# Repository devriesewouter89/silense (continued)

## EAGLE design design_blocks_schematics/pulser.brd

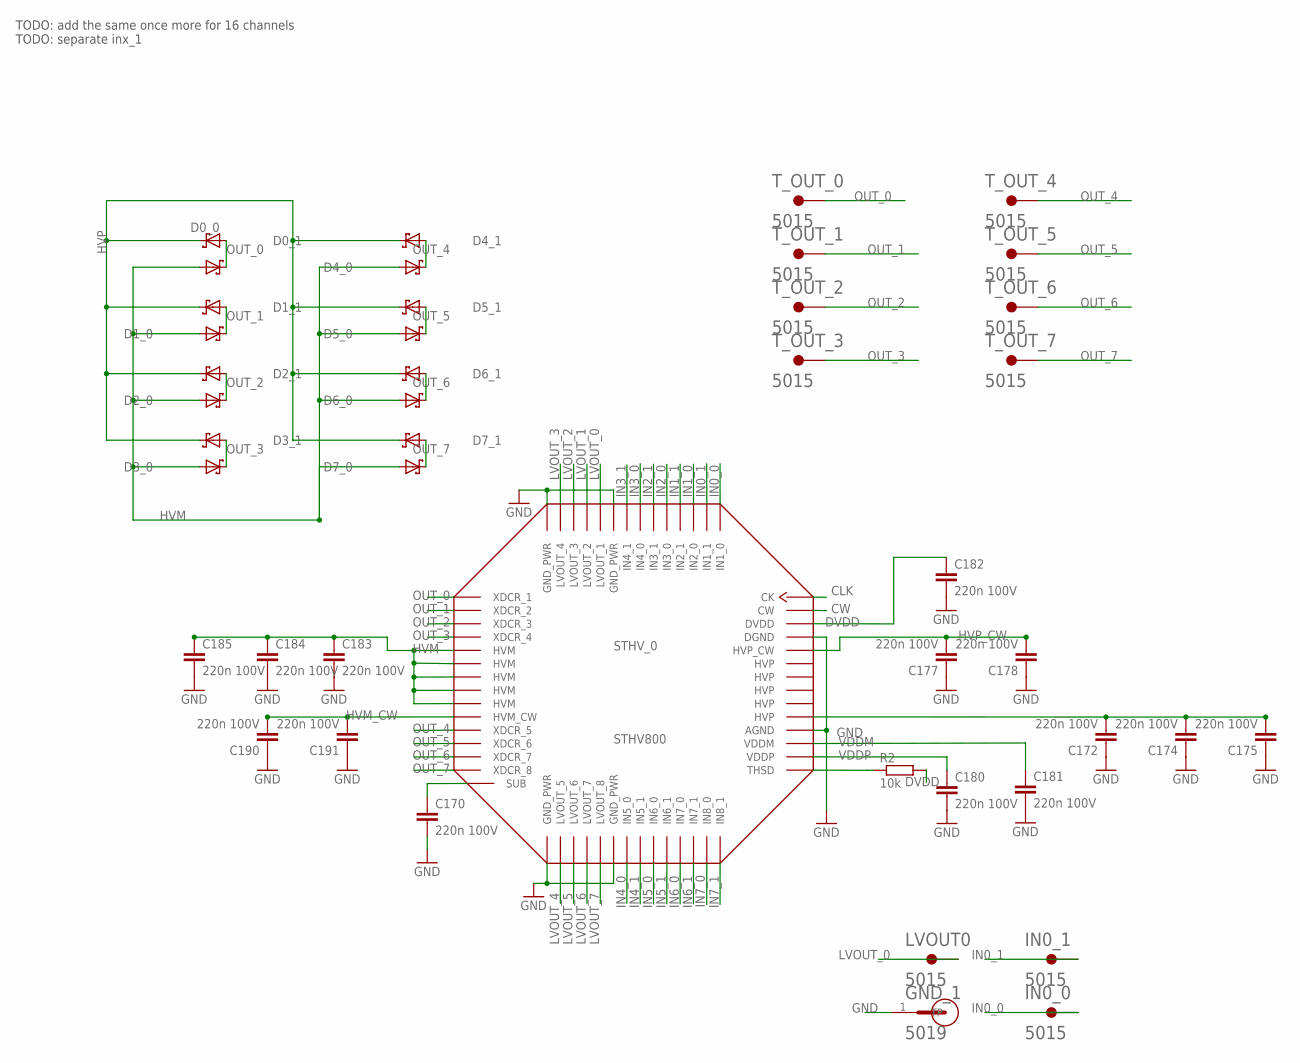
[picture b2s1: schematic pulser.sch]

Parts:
C170, C172, C174, C175, C177, C178, C180, C181, C182, C183, C184, C185, C190, C191: 220n 100V; C0805
D0_0, D0_1, D1_0, D1_1, D2_0, D2_1, D3_0, D3_1, D4_0, D4_1, D5_0, D5_1, D6_0, D6_1, D7_0, D7_1: SBR1U200P1SBR1U200P1; POWERDI-123
GND_1: 5019; TP380X203
IN0_0, IN0_1: 5015; KEYSTONE_5015
LVOUT0: 5015; KEYSTONE_5015
R2: 10k; R0805
STHV_0: STHV800; TFLGA-56LD
T_OUT_0, T_OUT_1, T_OUT_2, T_OUT_3, T_OUT_4, T_OUT_5, T_OUT_6, T_OUT_7: 5015; KEYSTONE_5015

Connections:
CLK: STHV_0.CK
CW: STHV_0.CW
GND: C170.2, C172.1, C174.1, C175.1, C177.1, C178.1, C180.2, C181.2, C182.2, C183.2, C184.2, C185.2, C190.1, C191.1, GND_1.1, STHV_0.AGND, STHV_0.DGND, STHV_0.GND_PWR@1 (GND_PWR), STHV_0.GND_PWR@2 (GND_PWR), STHV_0.GND_PWR@3 (GND_PWR), STHV_0.GND_PWR@4 (GND_PWR)
HVM: C183.1, C184.1, C185.1, D0_1.A, D1_1.A, D2_1.A, D3_1.A, D4_1.A, D5_1.A, D6_1.A, D7_1.A, STHV_0.HVM@1 (HVM), STHV_0.HVM@2 (HVM), STHV_0.HVM@3 (HVM), STHV_0.HVM@4 (HVM), STHV_0.HVM@5 (HVM)
HVM_CW: C190.2, C191.2, STHV_0.HVM_CW
HVP: C172.2, C174.2, C175.2, D0_0.C, D1_0.C, D2_0.C, D3_0.C, D4_0.C, D5_0.C, D6_0.C, D7_0.C, STHV_0.HVP@1 (HVP), STHV_0.HVP@2 (HVP), STHV_0.HVP@3 (HVP), STHV_0.HVP@4 (HVP), STHV_0.HVP@5 (HVP)
HVP_CW: C177.2, C178.2, STHV_0.HVP_CW
IN0_0: IN0_0.1, STHV_0.IN1_0
IN0_1: IN0_1.1, STHV_0.IN1_1
IN1_0: STHV_0.IN2_0
IN1_1: STHV_0.IN2_1
IN2_0: STHV_0.IN3_0
IN2_1: STHV_0.IN3_1
IN3_0: STHV_0.IN4_0
IN3_1: STHV_0.IN4_1
IN4_0: STHV_0.IN5_0
IN4_1: STHV_0.IN5_1
IN5_0: STHV_0.IN6_0
IN5_1: STHV_0.IN6_1
IN6_0: STHV_0.IN7_0
IN6_1: STHV_0.IN7_1
IN7_0: STHV_0.IN8_0
IN7_1: STHV_0.IN8_1
LVOUT_0: LVOUT0.1, STHV_0.LVOUT_1
LVOUT_1: STHV_0.LVOUT_2
LVOUT_2: STHV_0.LVOUT_3
LVOUT_3: STHV_0.LVOUT_4
LVOUT_4: STHV_0.LVOUT_5
LVOUT_5: STHV_0.LVOUT_6
LVOUT_6: STHV_0.LVOUT_7
LVOUT_7: STHV_0.LVOUT_8
unnamed: R2.1, STHV_0.THSD
unnamed: C170.1, STHV_0.SUB
OUT_0: D0_0.A, D0_1.C, STHV_0.XDCR_1, T_OUT_0.1
OUT_1: D1_0.A, D1_1.C, STHV_0.XDCR_2, T_OUT_1.1
OUT_2: D2_0.A, D2_1.C, STHV_0.XDCR_3, T_OUT_2.1
OUT_3: D3_0.A, D3_1.C, STHV_0.XDCR_4, T_OUT_3.1
OUT_4: D4_0.A, D4_1.C, STHV_0.XDCR_5, T_OUT_4.1
OUT_5: D5_0.A, D5_1.C, STHV_0.XDCR_6, T_OUT_5.1
OUT_6: D6_0.A, D6_1.C, STHV_0.XDCR_7, T_OUT_6.1
OUT_7: D7_0.A, D7_1.C, STHV_0.XDCR_8, T_OUT_7.1
VDDM: C181.1, STHV_0.VDDM
VDDP: C180.1, STHV_0.VDDP

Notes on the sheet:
TODO: add the same once more for 16 channels TODO: separate inx_1

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
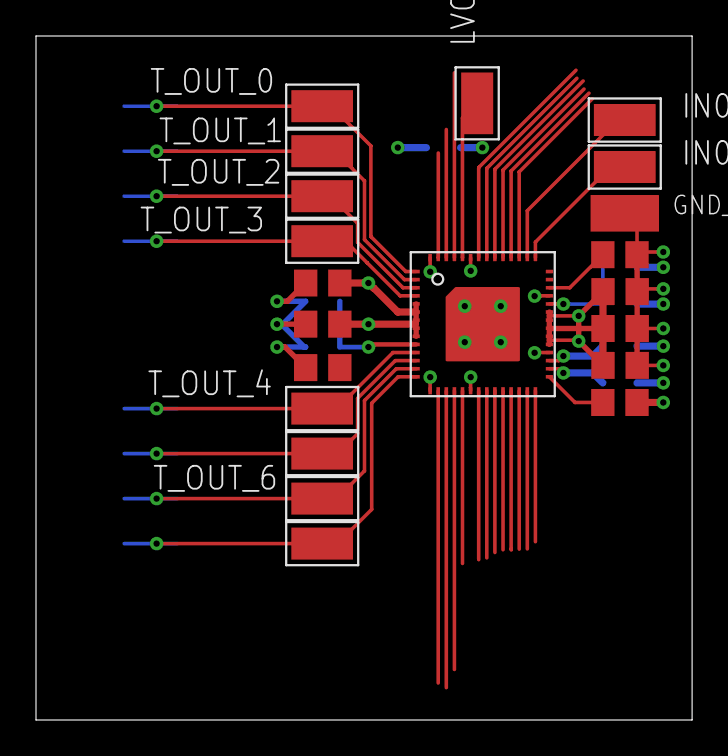
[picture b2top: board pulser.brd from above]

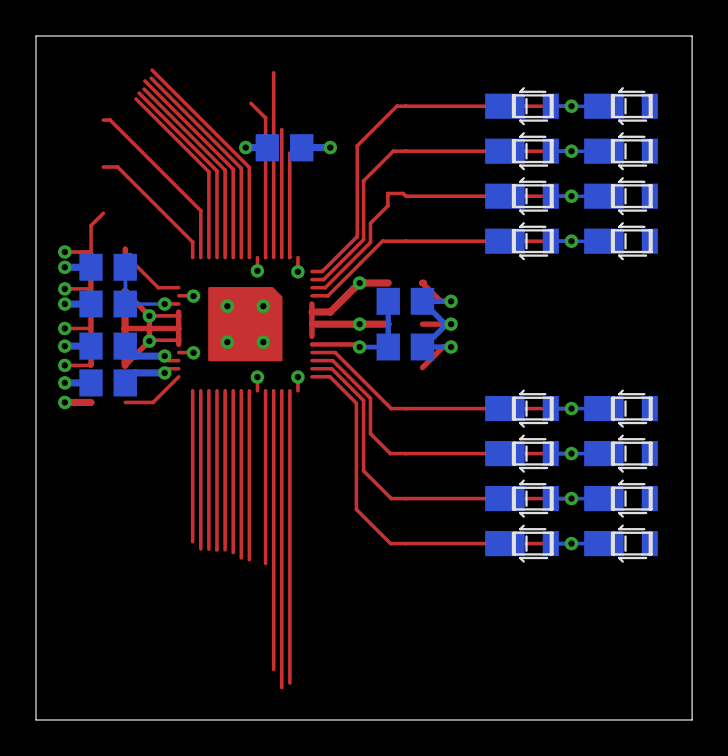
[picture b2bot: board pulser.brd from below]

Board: 2 copper layers, 36.5 x 38.0 mm, 44 parts (23 on the bottom side), 21 nets.

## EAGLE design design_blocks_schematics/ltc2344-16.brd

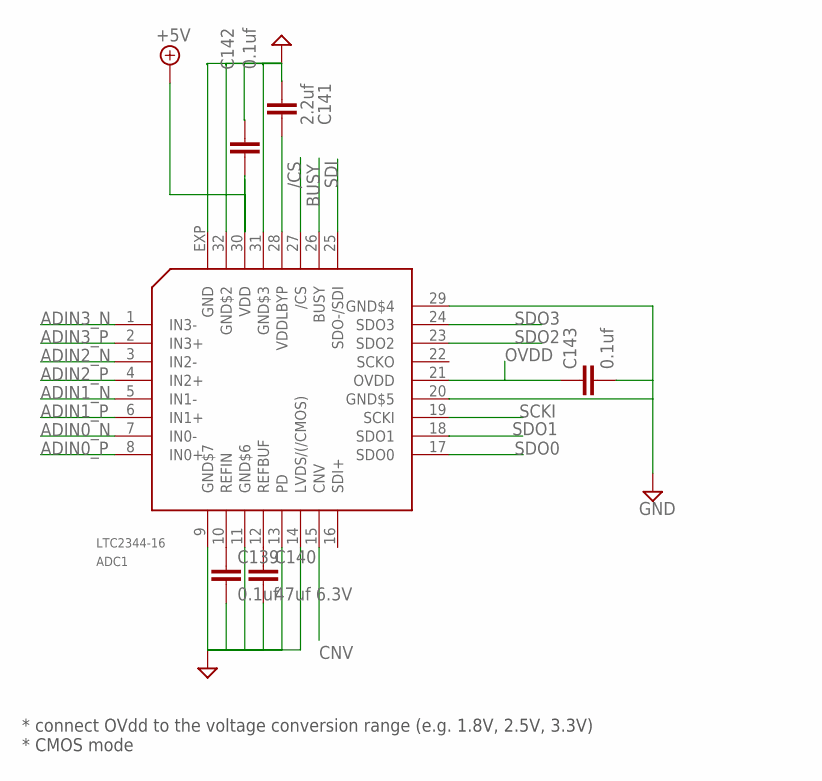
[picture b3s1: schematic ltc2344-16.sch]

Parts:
ADC1: LTC2344-16; QFN32
C139, C142, C143: 0.1uf; C0402
C140: 47uf 6.3V; C0603
C141: 2.2uf; C0402

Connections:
+5V: ADC1.30 (VDD), C142.1
/CS: ADC1.27 (/CS)
ADIN0_N: ADC1.7 (IN0-)
ADIN0_P: ADC1.8 (IN0+)
ADIN1_N: ADC1.5 (IN1-)
ADIN1_P: ADC1.6 (IN1+)
ADIN2_N: ADC1.3 (IN2-)
ADIN2_P: ADC1.4 (IN2+)
ADIN3_N: ADC1.1 (IN3-)
ADIN3_P: ADC1.2 (IN3+)
BUSY: ADC1.26 (BUSY)
CNV: ADC1.15 (CNV)
GND: ADC1.9 (GND$7), ADC1.11 (GND$6), ADC1.13 (PD), ADC1.14 (LVDS/(/CMOS)), ADC1.20 (GND$5), ADC1.29 (GND$4), ADC1.31 (GND$3), ADC1.32 (GND$2), ADC1.EXP (GND), C139.2, C140.2, C141.2, C142.2, C143.2
unnamed: ADC1.10 (REFIN), C139.1
unnamed: ADC1.12 (REFBUF), C140.1
unnamed: ADC1.28 (VDDLBYP), C141.1
OVDD: ADC1.21 (OVDD), C143.1
SCKI: ADC1.19 (SCKI)
SDI: ADC1.25 (SDO-/SDI)
SDO0: ADC1.17 (SDO0)
SDO1: ADC1.18 (SDO1)
SDO2: ADC1.23 (SDO2)
SDO3: ADC1.24 (SDO3)

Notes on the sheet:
* connect OVdd to the voltage conversion range (e.g. 1.8V, 2.5V, 3.3V) * CMOS mode

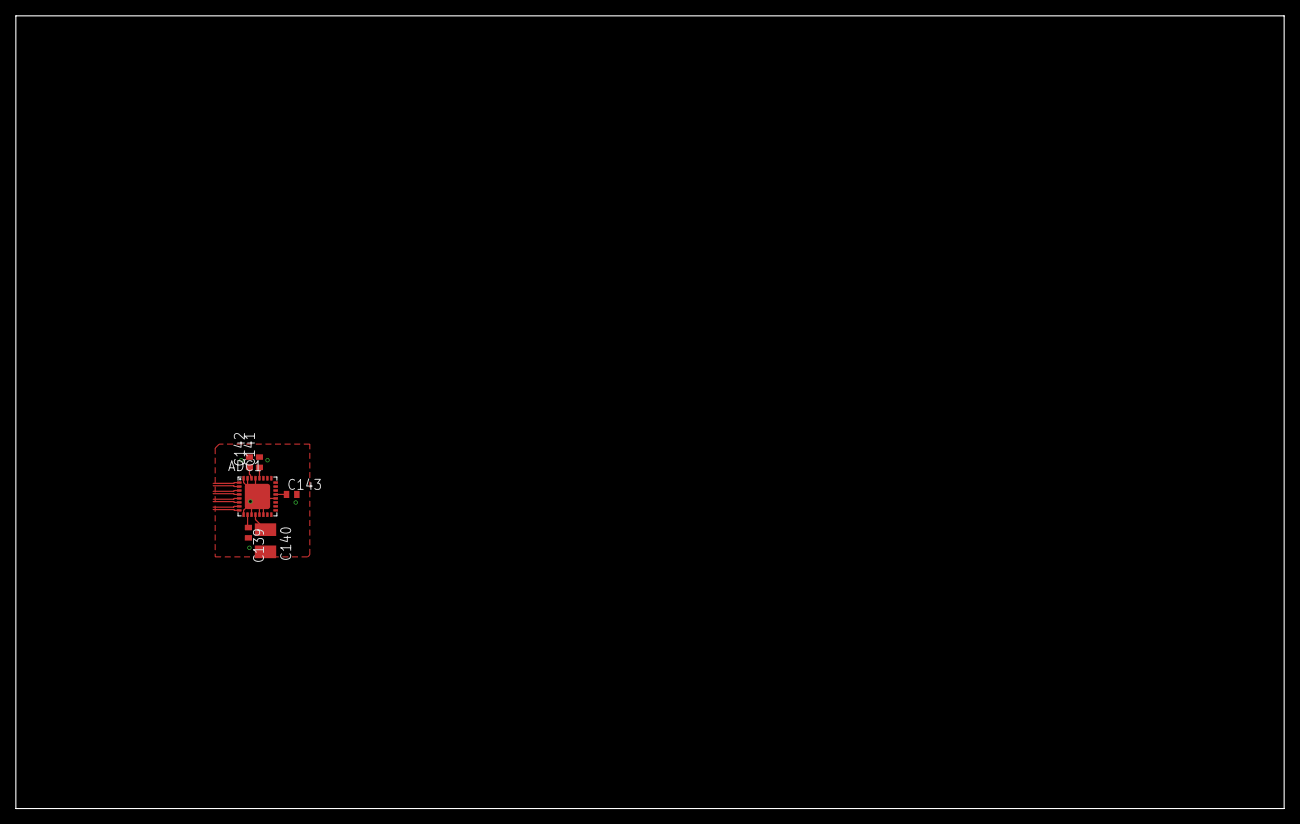
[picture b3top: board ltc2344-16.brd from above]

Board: 4 copper layers, 160.0 x 100.0 mm, 6 parts (0 on the bottom side), 6 nets.

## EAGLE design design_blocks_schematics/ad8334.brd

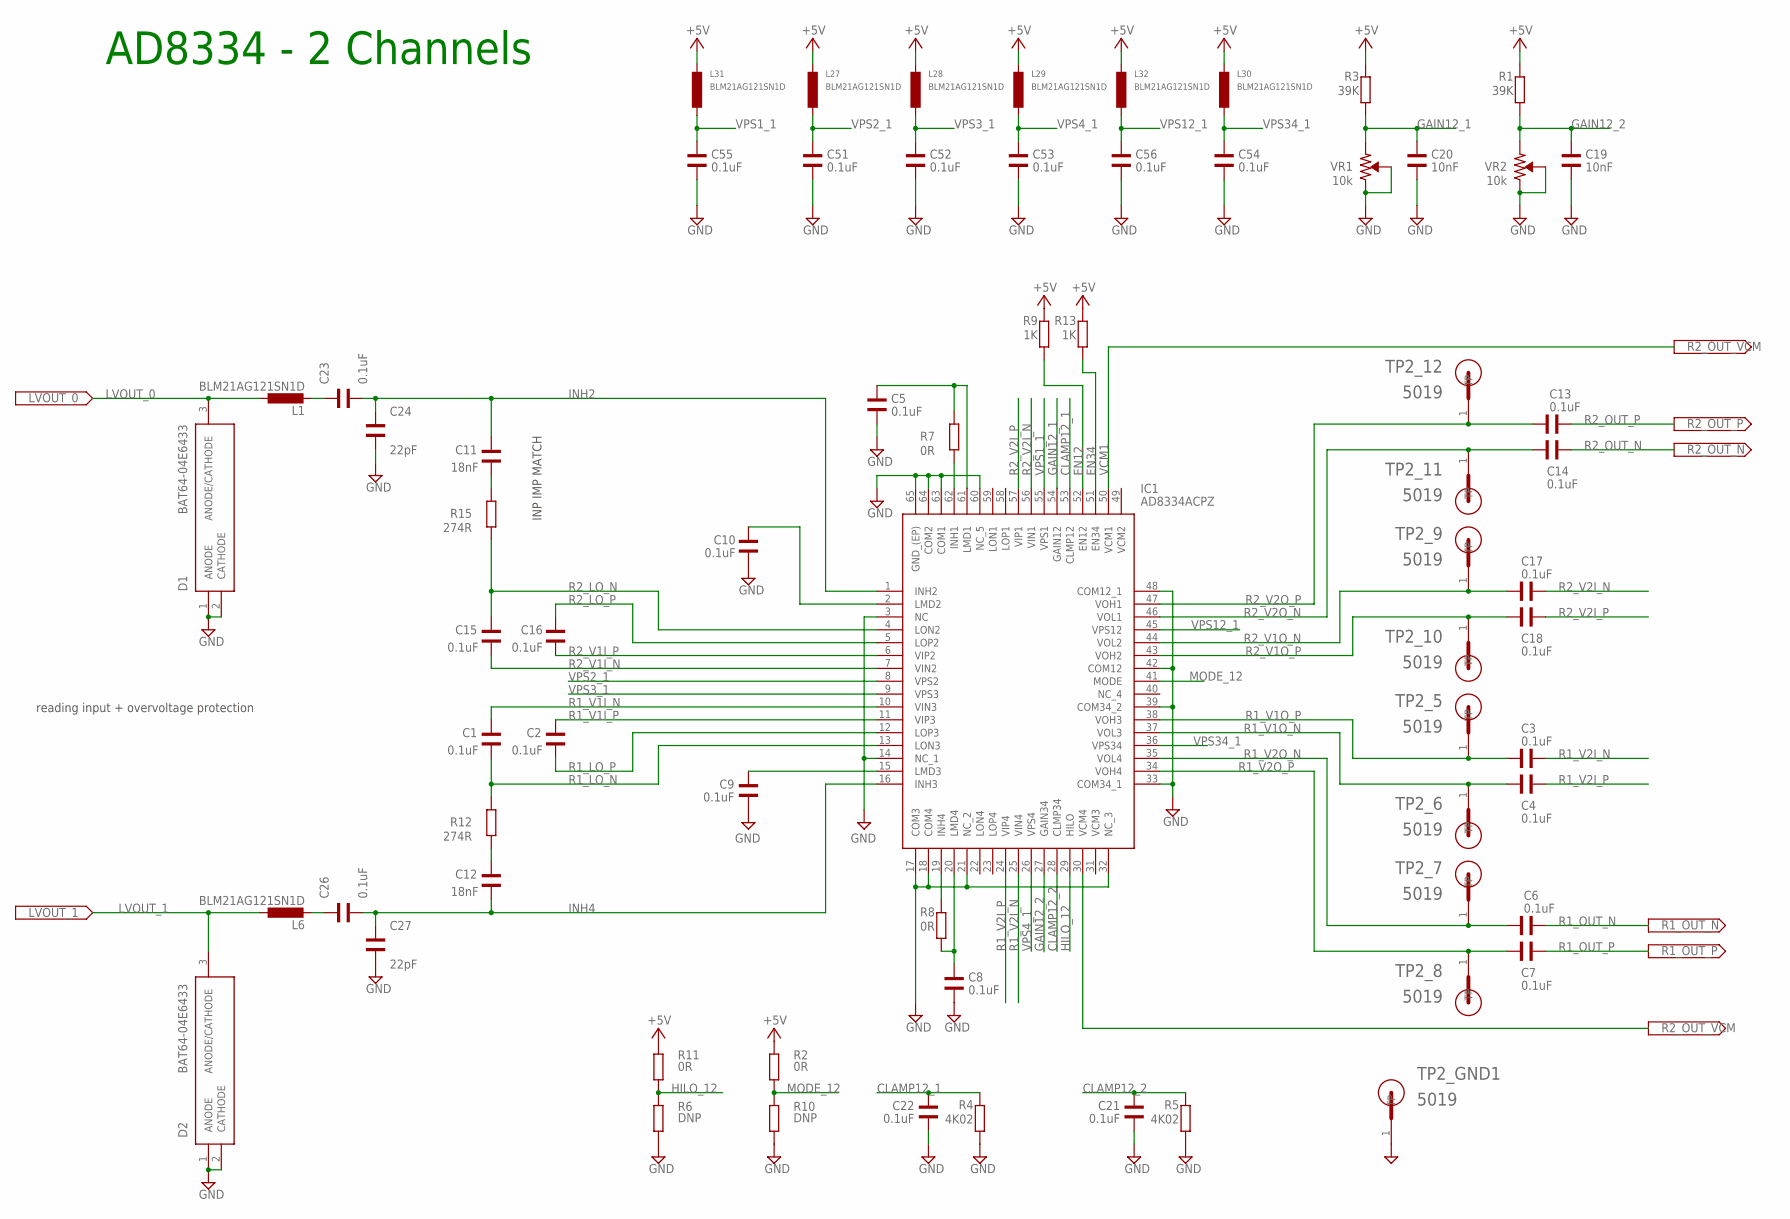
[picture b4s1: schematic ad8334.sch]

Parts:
C1, C2, C3, C4, C5, C6, C7, C8, C9, C10, C13, C14, C15, C16, C17, C18, C21, C22, C23, C26, C51, C52, C53, C54, C55, C56: 0.1uF; WCAP-CSGP_0402
C11, C12: 18nF; WCAP-CSGP_0402
C19, C20: 10nF; WCAP-CSGP_0402
C24, C27: 22pF; WCAP-CSGP_0402
D1, D2: BAT64-04E6433; SOT95P260X110-3N
IC1: AD8334ACPZ; QFN50P900X900X100-65N
L1, L6, L27, L28, L29, L30, L31, L32: BLM21AG121SN1D; L2012C
R1, R3: 39K; R0402
R2, R7, R8, R11: 0R; R0402
R4, R5: 4K02; R0402
R6, R10: DNP; R0402
R9, R13: 1K; R0402
R12, R15: 274R; R0402
TP2_5, TP2_6, TP2_7, TP2_8, TP2_9, TP2_10, TP2_11, TP2_12, TP2_GND1: 5019; TP380X203
VR1, VR2: 10k; TRIMPOT-SMD-TC33X

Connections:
+5V: L27.1, L28.1, L29.1, L30.1, L31.1, L32.1, R1.2, R2.2, R3.2, R9.2, R11.2, R13.2
CLAMP12_1: C22.1, IC1.53 (CLMP12), R4.2
CLAMP12_2: C21.1, IC1.28 (CLMP34), R5.2
EN12: IC1.52 (EN12), R9.1
EN34: IC1.51 (EN34), R13.1
GAIN12_1: C20.1, IC1.54 (GAIN12), R3.1, VR1.3 (CCW)
GAIN12_2: C19.1, IC1.27 (GAIN34), R1.1, VR2.3 (CCW)
GND: C5.2, C8.1, C9.1, C10.1, C19.2, C20.2, C21.2, C22.2, C24.1, C27.1, C51.1, C52.1, C53.1, C54.1, C55.1, C56.1, D1.1 (ANODE), D1.2 (CATHODE), D2.1 (ANODE), D2.2 (CATHODE), IC1.3 (NC), IC1.14 (NC_1), IC1.17 (COM3), IC1.18 (COM4), IC1.21 (NC_2), IC1.32 (NC_3), IC1.60 (NC_5), IC1.63 (COM1), IC1.64 (COM2), IC1.65 (GND_(EP)), R4.1, R5.1, R6.1, R10.1, TP2_GND1.1, VR1.1 (CW), VR1.2 (WIPER), VR2.1 (CW), VR2.2 (WIPER)
HILO_12: IC1.29 (HILO), R6.2, R11.1
INH2: C11.2, C23.1, C24.2, IC1.1 (INH2)
INH4: C12.1, C26.1, C27.2, IC1.16 (INH3)
LVOUT_0: D1.3 (ANODE/CATHODE), L1.1
LVOUT_1: D2.3 (ANODE/CATHODE), L6.1
MODE_12: IC1.41 (MODE), R2.1, R10.2
unnamed: C5.1, IC1.61 (LMD1), R7.2
unnamed: C8.2, IC1.20 (LMD4), R8.1
unnamed: IC1.33 (COM34_1), IC1.39 (COM34_2), IC1.42 (COM12), IC1.48 (COM12_1)
unnamed: C10.2, IC1.2 (LMD2)
unnamed: C9.2, IC1.15 (LMD3)
unnamed: C23.2, L1.2
unnamed: C11.1, R15.2
unnamed: C26.2, L6.2
unnamed: C12.2, R12.1
unnamed: IC1.19 (INH4), R8.2
R1_I: IC1.62 (INH1), R7.1
R1_LO_N: C1.1, IC1.13 (LON3), R12.2
R1_LO_P: C2.1, IC1.12 (LOP3)
R1_OUT_N: C6.2
R1_OUT_P: C7.2
R1_V1I_N: C1.2, IC1.10 (VIN3)
R1_V1I_P: C2.2, IC1.11 (VIP3)
R1_V1O_N: C4.1, IC1.37 (VOL3), TP2_6.1
R1_V1O_P: C3.1, IC1.38 (VOH3), TP2_5.1
R1_V2I_N: C3.2, IC1.25 (VIN4)
R1_V2I_P: C4.2, IC1.24 (VIP4)
R1_V2O_N: C6.1, IC1.35 (VOL4), TP2_7.1
R1_V2O_P: C7.1, IC1.34 (VOH4), TP2_8.1
R2_LO_N: C15.2, IC1.4 (LON2), R15.1
R2_LO_P: C16.2, IC1.5 (LOP2)
R2_OUT_N: C14.2
R2_OUT_P: C13.2
R2_V1I_N: C15.1, IC1.7 (VIN2)
R2_V1I_P: C16.1, IC1.6 (VIP2)
R2_V1O_N: C17.1, IC1.44 (VOL2), TP2_9.1
R2_V1O_P: C18.1, IC1.43 (VOH2), TP2_10.1
R2_V2I_N: C17.2, IC1.56 (VIN1)
R2_V2I_P: C18.2, IC1.57 (VIP1)
R2_V2O_N: C14.1, IC1.46 (VOL1), TP2_11.1
R2_V2O_P: C13.1, IC1.47 (VOH1), TP2_12.1
VCM1: IC1.50 (VCM1)
VCM3: IC1.30 (VCM4)
VPS1_1: C55.2, IC1.55 (VPS1), L31.2
VPS2_1: C51.2, IC1.8 (VPS2), L27.2
VPS3_1: C52.2, IC1.9 (VPS3), L28.2
VPS4_1: C53.2, IC1.26 (VPS4), L29.2
VPS12_1: C56.2, IC1.45 (VPS12), L32.2
VPS34_1: C54.2, IC1.36 (VPS34), L30.2

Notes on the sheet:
INP IMP MATCH
reading input + overvoltage protection
AD8334 - 2 Channels

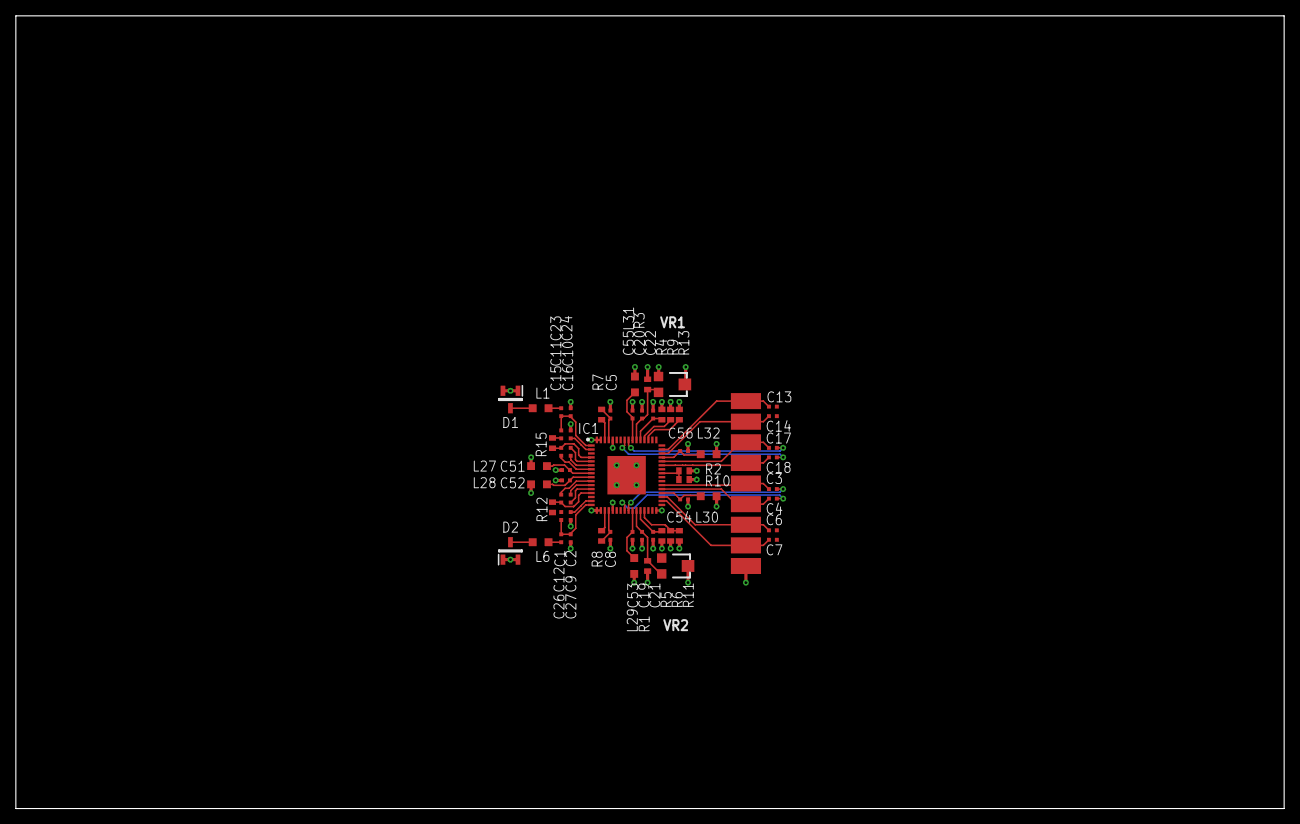
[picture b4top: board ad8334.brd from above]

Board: 2 copper layers, 160.0 x 100.0 mm, 68 parts (0 on the bottom side), 51 nets.

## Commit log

2019-08-16 added schematic of AD8334
2019-08-16 added pdf version of eagle files
2019-09-25 added eagle schematics
2019-09-25 removed unnecessary files
2019-09-29 AD8334 WIP
2019-09-29 WIP AD8334
2019-09-30 update: - some more todos - output connector added - input connections (16 channels)
2019-10-02 added powerblock for +-5V
2019-10-02 updated values and connections for +-5V
2019-10-02 added todos
2019-10-02 WIP AD8334: fixed netnames, checked NC, unused channels
2019-10-02 basic hierachical schematic, to be refined with ports
2019-10-02 updated hierarchy to 16 ch
2019-10-02 cleanup ADC sheet
2019-10-02 WIP Driver sheet
2019-10-02 added design blocks schematics folder
2019-10-02 moving ad8334 schematic to seperate project to generate design block
2019-10-02 further cleanup of todos
2019-10-02 added design block for sthv800 pulser chip
2019-10-03 finalized schematic
2019-10-03 routed input section
2019-10-03 routing 75% done
2019-10-03 routing done
2019-10-03 added simulations
2019-10-03 added design block schematic for lt8471
2019-10-03 added design blocks for 3v3 and 5v deduction
2019-10-07 added start for ltc2344-16 design block
2019-10-07 splitted simulations for envelope detection
2019-10-07 cleaned up schematic of ADC
2019-10-07 update on adc
2019-10-07 added design blocks for: AD8334 (2 channels in use) ltc2344-16: 4 channel ADC CMOS 2.5V compatible
2019-10-07 cleaned up schematic of sthv_800
2019-10-07 pulser layout WIP
2019-10-07 pulser layout done
2019-10-07 updated board size of dbl added envelope detection: - simulation - design block
2019-10-07 sthv800: updated board size & made design block
2019-10-07 added backup files of eagle
2019-10-07 removed simulation graphs
2019-10-07 sthv800 update: connected dvdd & vddp
2019-10-07 main board: added all fpga connections
2019-10-08 missing .sch from previous commit
2019-10-08 updated .gitignore and removed local eagle history files
2019-10-08 fixed refdes position on ltc2344 design block
2019-10-08 updated input output netnames
2019-10-08 updated input/output net names
2019-10-08 schematic done except for power
2019-10-09 merge
2019-10-09 cleanup schematic/WIP layout
2019-10-09 minor cleanup input connections
2019-10-11 reverted silense.sch to 1fa5b70, ignoring changes from wouter to this file only
2019-10-18 moved design blocks to separate repo
2019-10-25 Backlink to CADLAB.io has been added.
